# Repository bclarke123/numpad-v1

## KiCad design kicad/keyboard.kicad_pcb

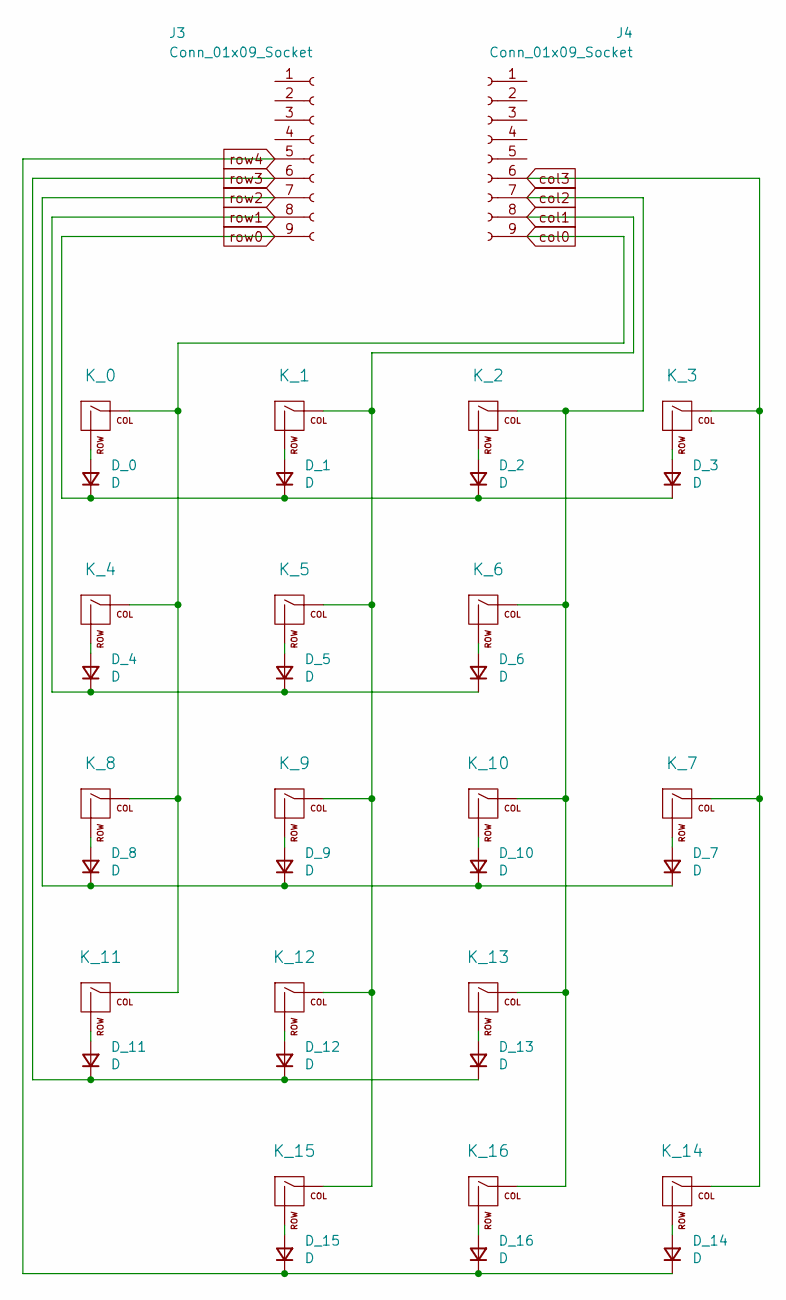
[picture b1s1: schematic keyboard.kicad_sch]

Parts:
D_0, D_1, D_2, D_3, D_4, D_5, D_6, D_7, D_8, D_9, D_10, D_11, D_12, D_13, D_14, D_15, D_16: D; D_A-405_P5.08mm_Vertical_AnodeUp
J3, J4: Conn_01x09_Socket; PinSocket_1x09_P2.54mm_Vertical
K_0, K_1, K_2, K_3, K_4, K_5, K_6, K_8, K_9, K_10, K_11, K_12, K_13, K_16: KEYSW; MX-1U-NoLED
K_7, K_14, K_15: KEYSW; MX-2U-NoLED

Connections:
unnamed: D_0.2 (A), K_0.2 (ROW)
unnamed: D_1.2 (A), K_1.2 (ROW)
unnamed: D_2.2 (A), K_2.2 (ROW)
unnamed: D_3.2 (A), K_3.2 (ROW)
unnamed: D_4.2 (A), K_4.2 (ROW)
unnamed: D_5.2 (A), K_5.2 (ROW)
unnamed: D_6.2 (A), K_6.2 (ROW)
unnamed: D_7.2 (A), K_7.2 (ROW)
unnamed: D_8.2 (A), K_8.2 (ROW)
unnamed: D_9.2 (A), K_9.2 (ROW)
unnamed: D_10.2 (A), K_10.2 (ROW)
unnamed: D_11.2 (A), K_11.2 (ROW)
unnamed: D_12.2 (A), K_12.2 (ROW)
unnamed: D_13.2 (A), K_13.2 (ROW)
unnamed: D_14.2 (A), K_14.2 (ROW)
unnamed: D_15.2 (A), K_15.2 (ROW)
unnamed: D_16.2 (A), K_16.2 (ROW)
col0: J4.9, K_0.1 (COL), K_4.1 (COL), K_8.1 (COL), K_11.1 (COL)
col1: J4.8, K_1.1 (COL), K_5.1 (COL), K_9.1 (COL), K_12.1 (COL), K_15.1 (COL)
col2: J4.7, K_2.1 (COL), K_6.1 (COL), K_10.1 (COL), K_13.1 (COL), K_16.1 (COL)
col3: J4.6, K_3.1 (COL), K_7.1 (COL), K_14.1 (COL)
row0: D_0.1 (K), D_1.1 (K), D_2.1 (K), D_3.1 (K), J3.9
row1: D_4.1 (K), D_5.1 (K), D_6.1 (K), J3.8
row2: D_7.1 (K), D_8.1 (K), D_9.1 (K), D_10.1 (K), J3.7
row3: D_11.1 (K), D_12.1 (K), D_13.1 (K), J3.6
row4: D_14.1 (K), D_15.1 (K), D_16.1 (K), J3.5

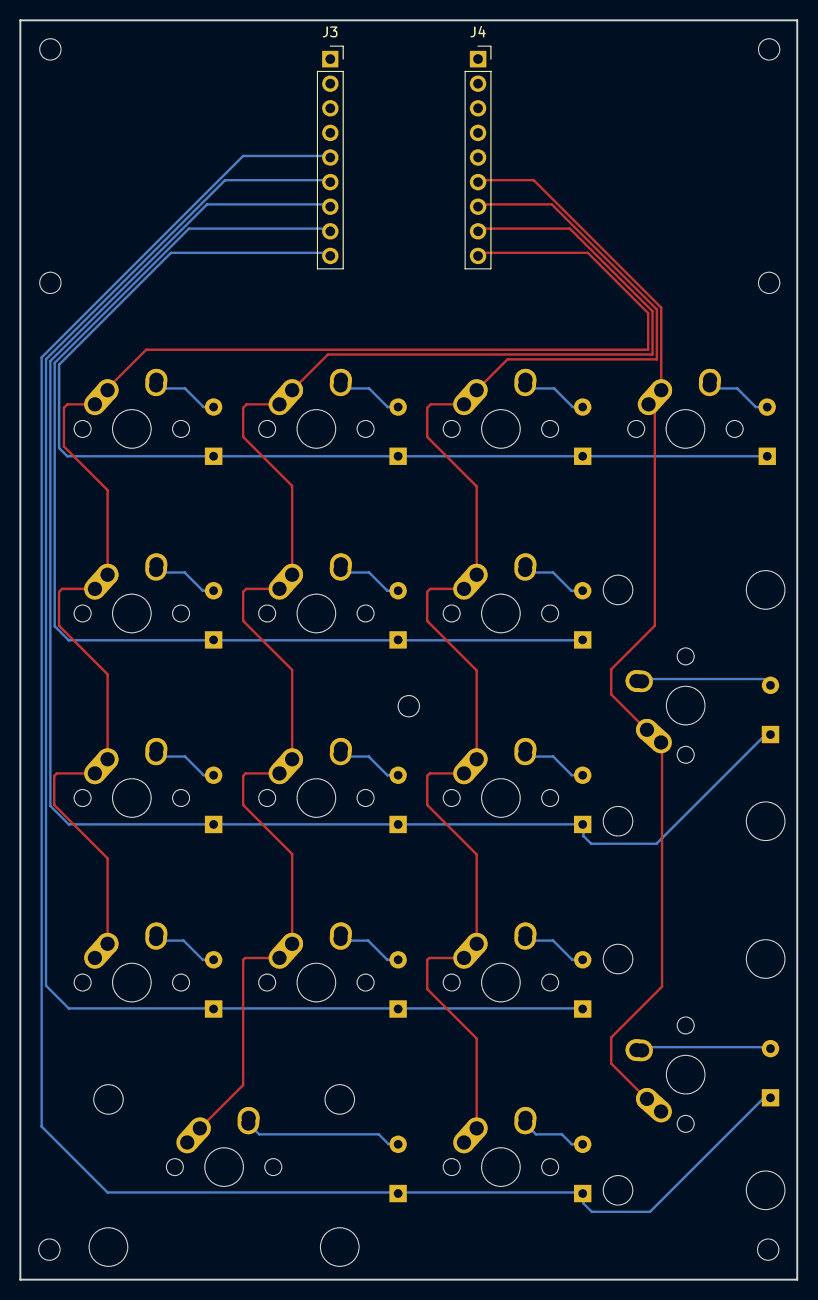
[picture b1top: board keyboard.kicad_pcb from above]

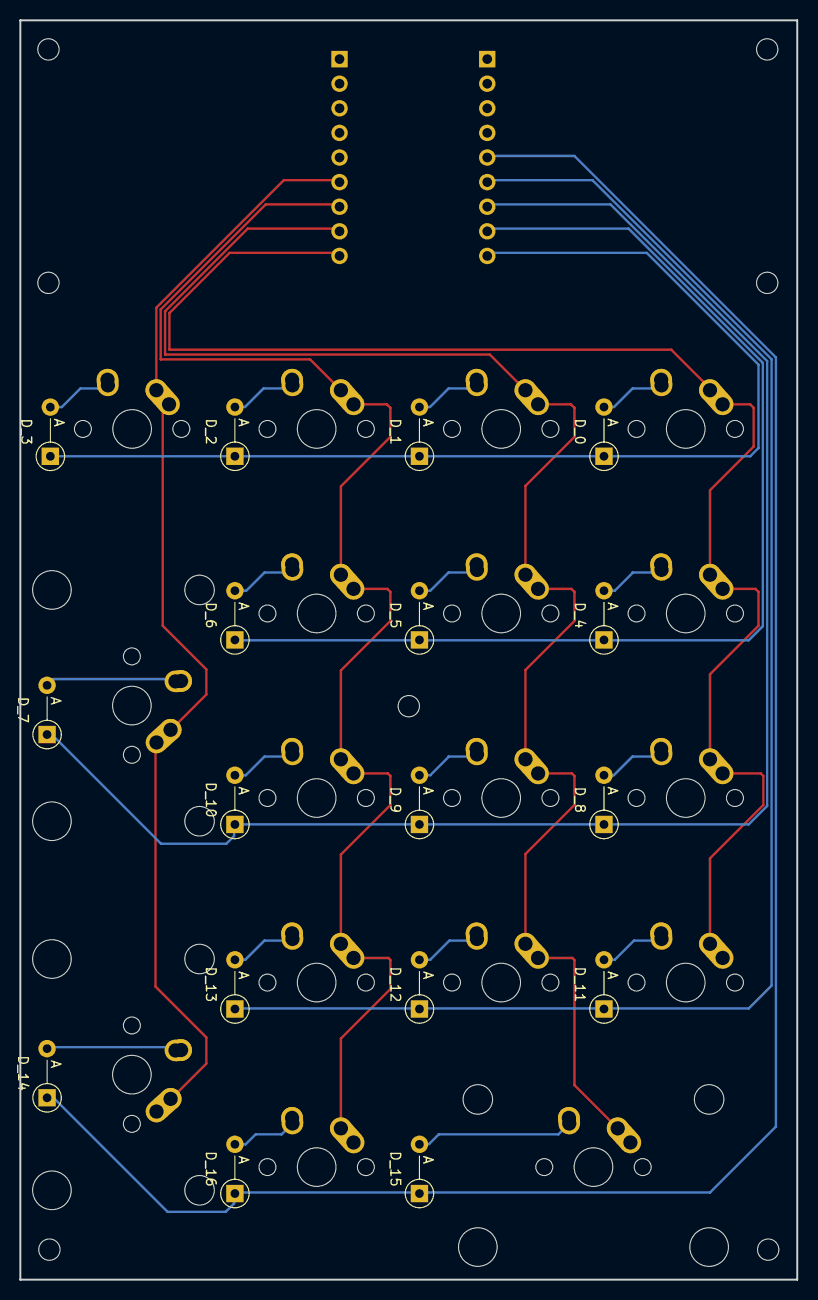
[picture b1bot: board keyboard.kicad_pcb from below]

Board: 2 copper layers, 80.2 x 130.0 mm, 36 parts (17 on the bottom side), 26 nets.
